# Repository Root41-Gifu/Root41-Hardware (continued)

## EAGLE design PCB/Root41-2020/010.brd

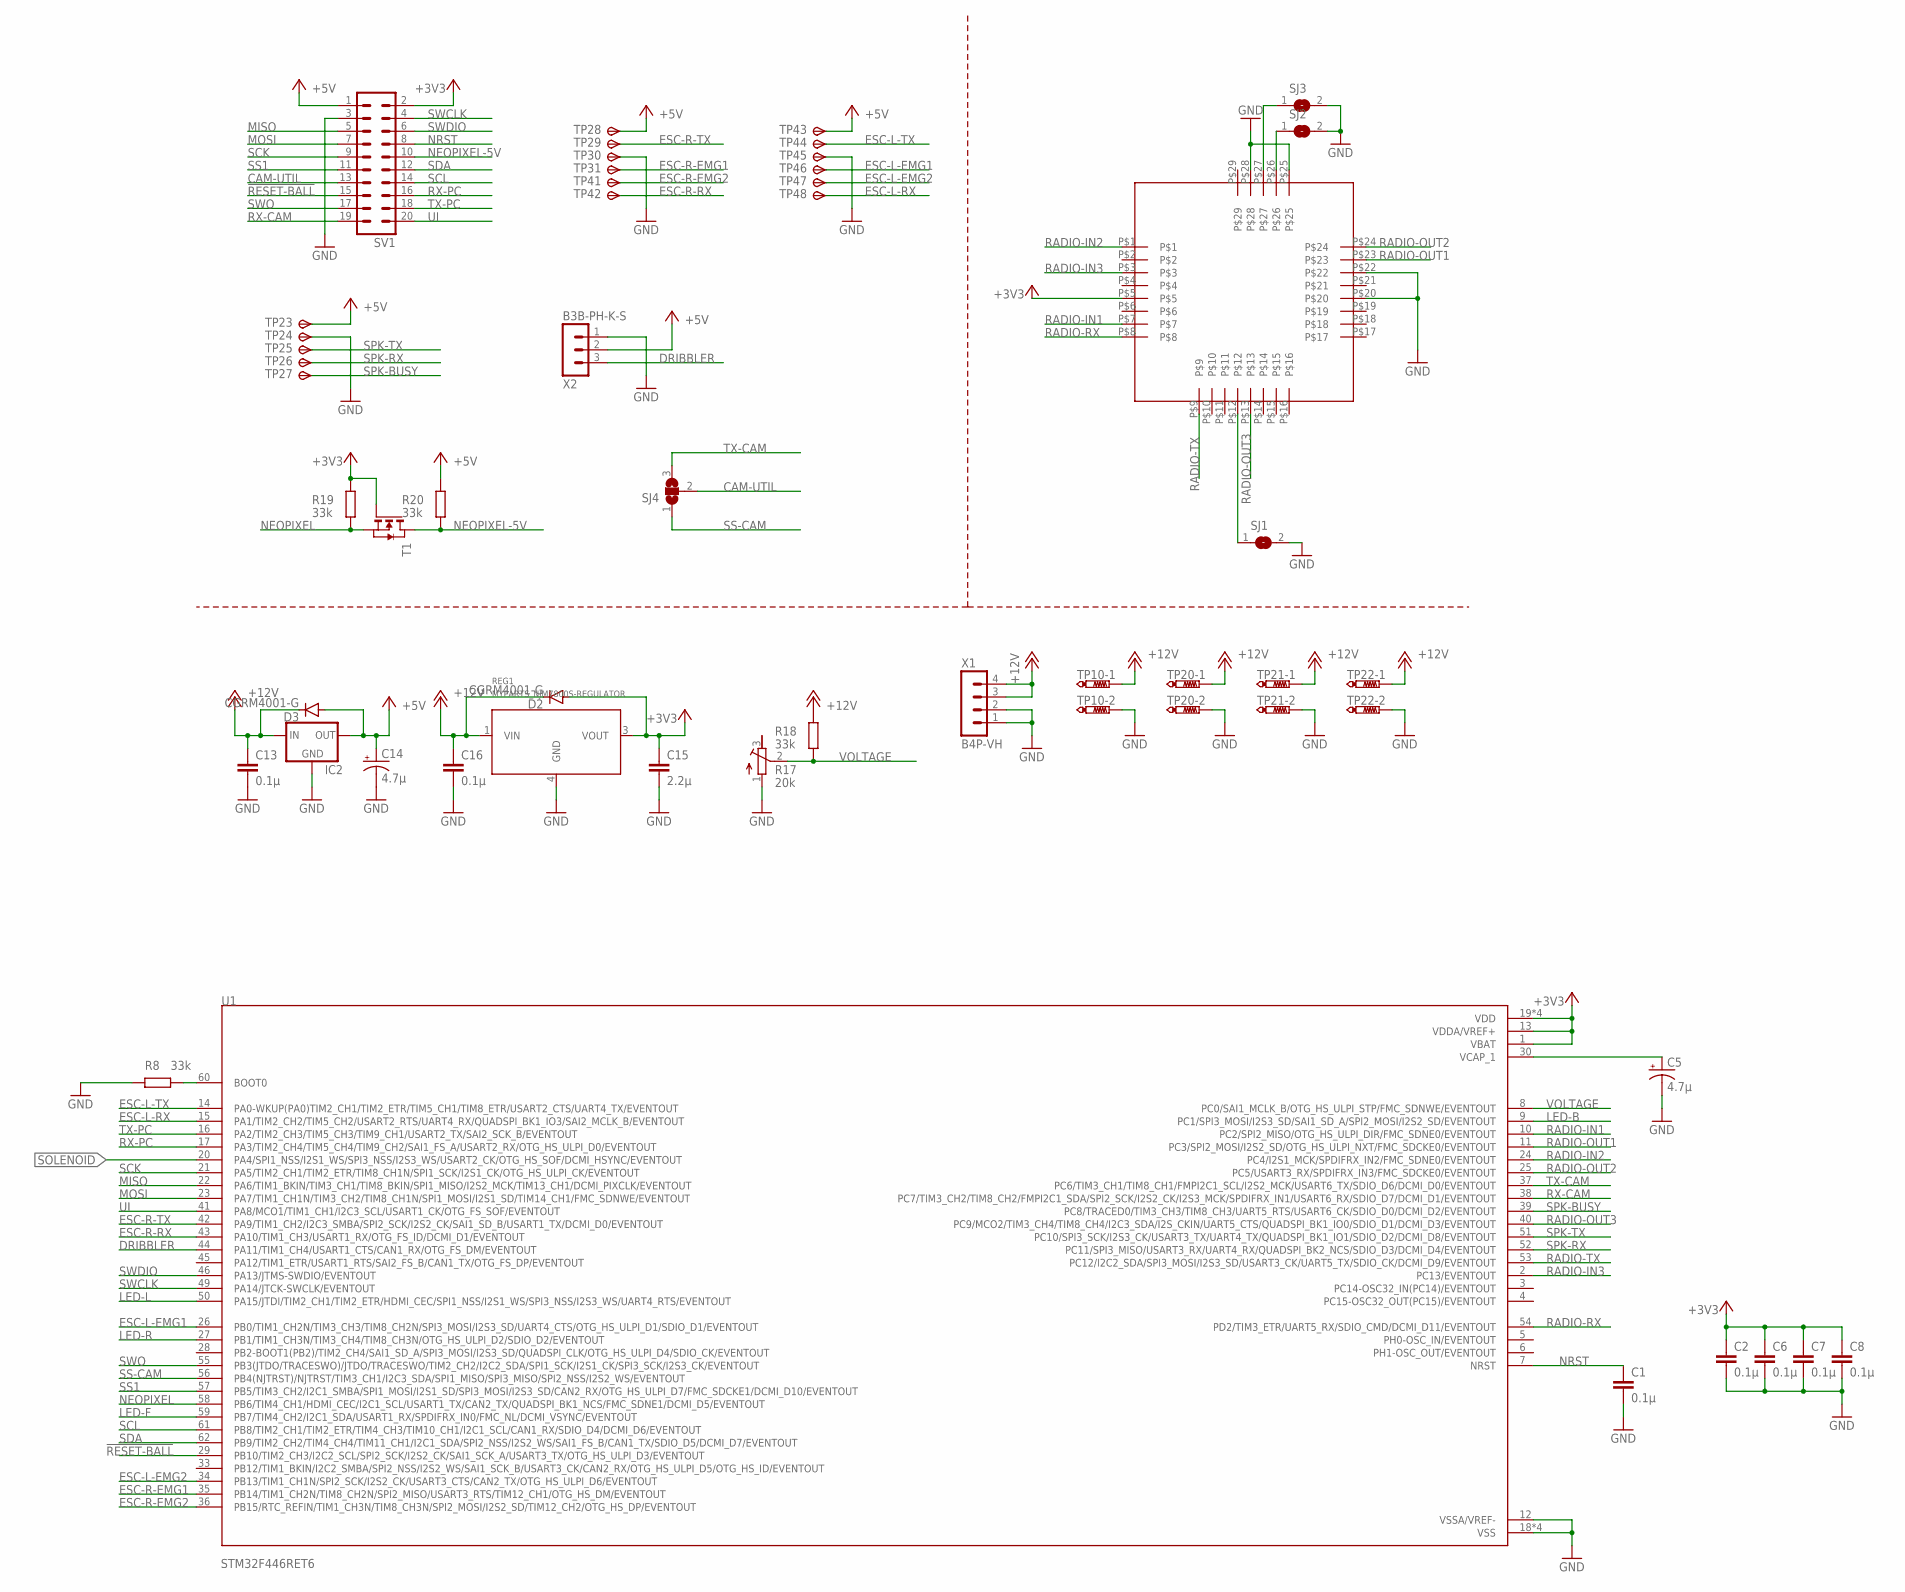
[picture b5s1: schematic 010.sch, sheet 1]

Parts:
C1, C2, C6, C7, C8, C13, C16: 0.1μ; C1608
C5, C14: 4.7μ; SANYO-OSCON_SMD_B6
C15: 2.2μ; C1608
D2, D3: CGRM4001-G; SOD-123_MINI-SMA
IC2: 78XXS
R8, R18, R19, R20: 33k; R0603
R17: 20k; RTRIM3296W
REG1: MYPARTS_NJM7800S-REGULATOR; MYPARTS_D-PAK_TO252AA
SJ1, SJ2, SJ3: SJ
SJ4: SJ2W; SJ_2
SV1: ML20
T1: NMOSSOT23; SOT-23
TP10, TP20, TP21, TP22: PTR2; P2-38-17
TP23, TP28, TP43: TPSTP09SQ; TP09SQ
TP24, TP25, TP26, TP27, TP29, TP30, TP31, TP41, TP42, TP44, TP45, TP46, TP47, TP48: TPSTP09R; TP09R
U1: STM32F446RET6; QFP50P1200X1200X160-64N
U$1: LITE
X1: B4P-VH
X2: B3B-PH-K-S

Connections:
!RESET-BALL: SV1.15, U1.29 (PB10/TIM2_CH3/I2C2_SCL/SPI2_SCK/I2S2_CK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)
+3V3: C2.1, C6.1, C7.1, C8.1, C15.1, D2.A, R19.2, REG1.3 (VOUT), SV1.2, T1.3 (G), U1.1 (VBAT), U1.13 (VDDA/VREF+), U1.19 (VDD), U1.32 (VDD), U1.48 (VDD), U1.64 (VDD), U$1.P$5; also elsewhere on the board
+5V: C14.+, D3.A, IC2.OUT, R20.2, SV1.1, TP23.TP, TP28.TP, TP43.TP, X2.2; also elsewhere on the board
+12V: C13.1, C16.1, D2.C, D3.C, IC2.IN, R18.2, REG1.1 (VIN), TP10.TP-1, TP20.TP-1, TP21.TP-1, TP22.TP-1, X1.3, X1.4; also elsewhere on the board
CAM-UTIL: SJ4.2, SV1.13
DRIBBLER: U1.44 (PA11/TIM1_CH4/USART1_CTS/CAN1_RX/OTG_FS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), X2.3
ESC-L-EMG1: TP46.TP, U1.26 (PB0/TIM1_CH2N/TIM3_CH3/TIM8_CH2N/SPI3_M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)
ESC-L-EMG2: TP47.TP, U1.34 (PB13/TIM1_CH1N/SPI2_SCK/I2S2_CK/USART3_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)
ESC-L-RX: TP48.TP, U1.15 (PA1/TIM2_CH2/TIM5_CH2/USART2_RTS/UART4_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)
ESC-L-TX: TP44.TP, U1.14 (PA0-WKUP(PA0)TIM2_CH1/TIM2_ETR/TIM5_CH1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)
ESC-R-EMG1: TP31.TP, U1.35 (PB14/TIM1_CH2N/TIM8_CH2N/SPI2_MISO/USAR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)
ESC-R-EMG2: TP41.TP, U1.36 (PB15/RTC_REFIN/TIM1_CH3N/TIM8_CH3N/SPI2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)
ESC-R-RX: TP42.TP, U1.43 (PA10/TIM1_CH3/USART1_RX/OTG_FS_ID/DCMI_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)
ESC-R-TX: TP29.TP, U1.42 (PA9/TIM1_CH2/I2C3_SMBA/SPI2_SCK/I2S2_CK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)
GND: C1.2, C2.2, C5.-, C6.2, C7.2, C8.2, C13.2, C14.-, C15.2, C16.2, IC2.GND, R8.2, R17.1 (A), REG1.4 (GND), SJ1.2, SJ2.2, SJ3.2, SV1.3, TP10.TP-2, TP20.TP-2, TP21.TP-2, TP22.TP-2, TP24.TP, TP30.TP, TP45.TP, U1.12 (VSSA/VREF-), U1.18 (VSS), U1.31 (VSS), U1.47 (VSS), U1.63 (VSS), U$1.P$20, U$1.P$22, U$1.P$25, U$1.P$28, X1.1, X1.2, X2.1; also elsewhere on the board
LED-B: U1.9 (PC1/SPI3_MOSI/I2S3_SD/SAI1_SD_A/SPI2_MO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); also elsewhere on the board
LED-F: U1.59 (PB7/TIM4_CH2/I2C1_SDA/USART1_RX/SPDIFRX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); also elsewhere on the board
LED-L: U1.50 (PA15/JTDI/TIM2_CH1/TIM2_ETR/HDMI_CEC/SP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); also elsewhere on the board
LED-R: U1.27 (PB1/TIM1_CH3N/TIM3_CH4/TIM8_CH3N/OTG_HS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); also elsewhere on the board
MISO: SV1.5, U1.22 (PA6/TIM1_BKIN/TIM3_CH1/TIM8_BKIN/SPI1_M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)
MOSI: SV1.7, U1.23 (PA7/TIM1_CH1N/TIM3_CH2/TIM8_CH1N/SPI1_M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)
unnamed: R8.1, U1.60 (BOOT0)
unnamed: C5.+, U1.30 (VCAP_1)
unnamed: SJ1.1, U$1.P$12
unnamed: SJ2.1, U$1.P$26
unnamed: SJ3.1, U$1.P$27
NEOPIXEL: R19.1, T1.2 (S), U1.58 (PB6/TIM4_CH1/HDMI_CEC/I2C1_SCL/USART1_T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)
NEOPIXEL-5V: R20.1, SV1.10, T1.1 (D)
NRST: C1.1, SV1.8, U1.7 (NRST)
RADIO-IN1: U1.10 (PC2/SPI2_MISO/OTG_HS_ULPI_DIR/FMC_SDNE0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), U$1.P$7
RADIO-IN2: U1.24 (PC4/I2S1_MCK/SPDIFRX_IN2/FMC_SDNE0/EVEN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), U$1.P$1
RADIO-IN3: U1.2 (PC13/EVENTOUT), U$1.P$3
RADIO-OUT1: U1.11 (PC3/SPI2_MOSI/I2S2_SD/OTG_HS_ULPI_NXT/F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), U$1.P$23
RADIO-OUT2: U1.25 (PC5/USART3_RX/SPDIFRX_IN3/FMC_SDCKE0/EV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), U$1.P$24
RADIO-OUT3: U1.40 (PC9/MCO2/TIM3_CH4/TIM8_CH4/I2C3_SDA/I2S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), U$1.P$13
RADIO-RX: U1.54 (PD2/TIM3_ETR/UART5_RX/SDIO_CMD/DCMI_D11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), U$1.P$8
RADIO-TX: U1.53 (PC12/I2C2_SDA/SPI3_MOSI/I2S3_SD/USART3_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), U$1.P$9
RX-CAM: SV1.19, U1.38 (PC7/TIM3_CH2/TIM8_CH2/FMPI2C1_SDA/SPI2_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)
RX-PC: SV1.16, U1.17 (PA3/TIM2_CH4/TIM5_CH4/TIM9_CH2/SAI1_FS_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)
SCK: SV1.9, U1.21 (PA5/TIM2_CH1/TIM2_ETR/TIM8_CH1N/SPI1_SC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)
SCL: SV1.14, U1.61 (PB8/TIM2_CH1/TIM2_ETR/TIM4_CH3/TIM10_CH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); also elsewhere on the board
SDA: SV1.12, U1.62 (PB9/TIM2_CH2/TIM4_CH4/TIM11_CH1/I2C1_SD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); also elsewhere on the board
SOLENOID: U1.20 (PA4/SPI1_NSS/I2S1_WS/SPI3_NSS/I2S3_WS/U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); also elsewhere on the board
SPK-BUSY: TP27.TP, U1.39 (PC8/TRACED0/TIM3_CH3/TIM8_CH3/UART5_RTS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)
SPK-RX: TP26.TP, U1.52 (PC11/SPI3_MISO/USART3_RX/UART4_RX/QUADS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)
SPK-TX: TP25.TP, U1.51 (PC10/SPI3_SCK/I2S3_CK/USART3_TX/UART4_T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)
SS1: SV1.11, U1.57 (PB5/TIM3_CH2/I2C1_SMBA/SPI1_MOSI/I2S1_S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)
SS-CAM: SJ4.1, U1.56 (PB4(NJTRST)/NJTRST/TIM3_CH1/I2C3_SDA/SP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)
SWCLK: SV1.4, U1.49 (PA14/JTCK-SWCLK/EVENTOUT)
SWDIO: SV1.6, U1.46 (PA13/JTMS-SWDIO/EVENTOUT)
SWO: SV1.17, U1.55 (PB3(JTDO/TRACESWO)/JTDO/TRACESWO/TIM2_C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)
TX-CAM: SJ4.3, U1.37 (PC6/TIM3_CH1/TIM8_CH1/FMPI2C1_SCL/I2S2_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)
TX-PC: SV1.18, U1.16 (PA2/TIM2_CH3/TIM5_CH3/TIM9_CH1/USART2_T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)
UI: SV1.20, U1.41 (PA8/MCO1/TIM1_CH1/I2C3_SCL/USART1_CK/OT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)
VOLTAGE: R17.2 (S), R18.1, U1.8 (PC0/SAI1_MCLK_B/OTG_HS_ULPI_STP/FMC_SDN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)

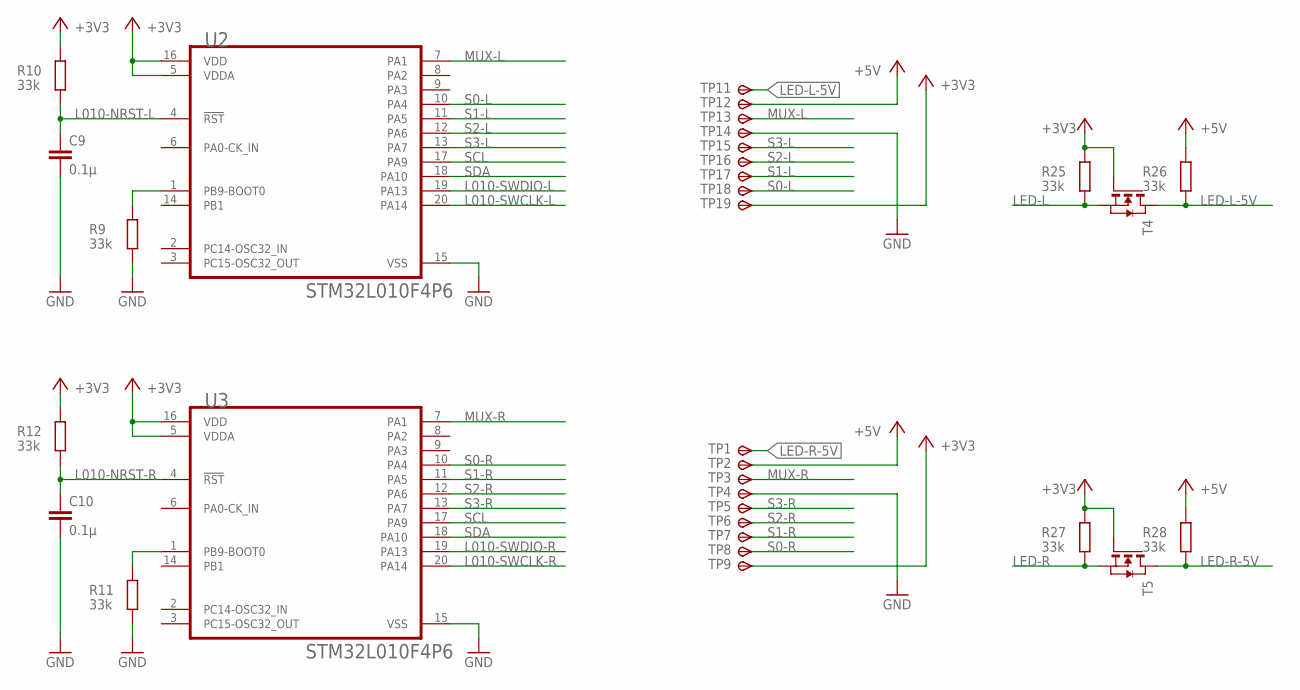
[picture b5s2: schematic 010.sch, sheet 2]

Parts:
C9, C10: 0.1μ; C1608
R9, R10, R11, R12, R25, R26, R27, R28: 33k; R0603
T4, T5: NMOSSOT23; SOT-23
TP1, TP11: TPSTP09SQ; TP09SQ
TP2, TP3, TP4, TP5, TP6, TP7, TP8, TP9, TP12, TP13, TP14, TP15, TP16, TP17, TP18, TP19: TPSTP09R; TP09R
U2, U3: STMICROELECTRONICS_STM32L010F4P6STMICROELECTRONIC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; STMICROELECTRONICS_STM32L010F4P6_2

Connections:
+3V3: R10.2, R12.2, R25.2, R27.2, T4.3 (G), T5.3 (G), TP9.TP, TP19.TP, U2.5 (VDDA), U2.16 (VDD), U3.5 (VDDA), U3.16 (VDD); also elsewhere on the board
+5V: R26.2, R28.2, TP2.TP, TP12.TP; also elsewhere on the board
GND: C9.2, C10.2, R9.1, R11.1, TP4.TP, TP14.TP, U2.15 (VSS), U3.15 (VSS); also elsewhere on the board
L010-NRST-L: C9.1, R10.1, U2.4 (!RST!)
L010-NRST-R: C10.1, R12.1, U3.4 (!RST!)
L010-SWCLK-L: U2.20 (PA14)
L010-SWCLK-R: U3.20 (PA14)
L010-SWDIO-L: U2.19 (PA13)
L010-SWDIO-R: U3.19 (PA13)
LED-L: R25.1, T4.2 (S); also elsewhere on the board
LED-L-5V: R26.1, T4.1 (D), TP11.TP
LED-R: R27.1, T5.2 (S); also elsewhere on the board
LED-R-5V: R28.1, T5.1 (D), TP1.TP
MUX-L: TP13.TP, U2.7 (PA1)
MUX-R: TP3.TP, U3.7 (PA1)
unnamed: R11.2, U3.1 (PB9-BOOT0)
unnamed: R9.2, U2.1 (PB9-BOOT0)
S0-L: TP18.TP, U2.10 (PA4)
S0-R: TP8.TP, U3.10 (PA4)
S1-L: TP17.TP, U2.11 (PA5)
S1-R: TP7.TP, U3.11 (PA5)
S2-L: TP16.TP, U2.12 (PA6)
S2-R: TP6.TP, U3.12 (PA6)
S3-L: TP15.TP, U2.13 (PA7)
S3-R: TP5.TP, U3.13 (PA7)
SCL: U2.17 (PA9), U3.17 (PA9); also elsewhere on the board
SDA: U2.18 (PA10), U3.18 (PA10); also elsewhere on the board

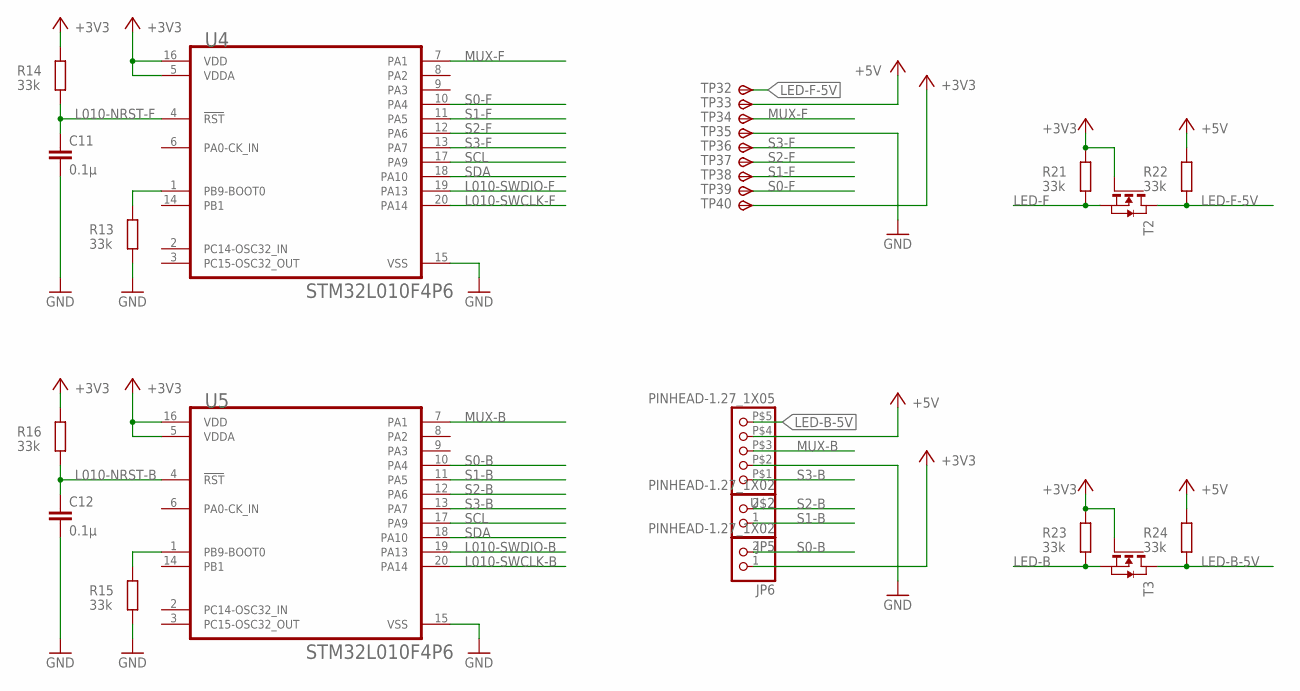
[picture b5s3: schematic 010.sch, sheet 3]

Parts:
C11, C12: 0.1μ; C1608
JP5, JP6: PINHEAD-1.27_1X02
R13, R14, R15, R16, R21, R22, R23, R24: 33k; R0603
T2, T3: NMOSSOT23; SOT-23
TP32: TPSTP09SQ; TP09SQ
TP33, TP34, TP35, TP36, TP37, TP38, TP39, TP40: TPSTP09R; TP09R
U4, U5: STMICROELECTRONICS_STM32L010F4P6STMICROELECTRONIC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; STMICROELECTRONICS_STM32L010F4P6_2
U$2: PINHEAD-1.27_1X05

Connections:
+3V3: JP6.1, R14.2, R16.2, R21.2, R23.2, T2.3 (G), T3.3 (G), TP40.TP, U4.5 (VDDA), U4.16 (VDD), U5.5 (VDDA), U5.16 (VDD); also elsewhere on the board
+5V: R22.2, R24.2, TP33.TP, U$2.P$4 (4); also elsewhere on the board
GND: C11.2, C12.2, R13.1, R15.1, TP35.TP, U4.15 (VSS), U5.15 (VSS), U$2.P$2 (2); also elsewhere on the board
L010-NRST-B: C12.1, R16.1, U5.4 (!RST!)
L010-NRST-F: C11.1, R14.1, U4.4 (!RST!)
L010-SWCLK-B: U5.20 (PA14)
L010-SWCLK-F: U4.20 (PA14)
L010-SWDIO-B: U5.19 (PA13)
L010-SWDIO-F: U4.19 (PA13)
LED-B: R23.1, T3.2 (S); also elsewhere on the board
LED-B-5V: R24.1, T3.1 (D), U$2.P$5 (5)
LED-F: R21.1, T2.2 (S); also elsewhere on the board
LED-F-5V: R22.1, T2.1 (D), TP32.TP
MUX-B: U5.7 (PA1), U$2.P$3 (3)
MUX-F: TP34.TP, U4.7 (PA1)
unnamed: R13.2, U4.1 (PB9-BOOT0)
unnamed: R15.2, U5.1 (PB9-BOOT0)
S0-B: JP6.2, U5.10 (PA4)
S0-F: TP39.TP, U4.10 (PA4)
S1-B: JP5.1, U5.11 (PA5)
S1-F: TP38.TP, U4.11 (PA5)
S2-B: JP5.2, U5.12 (PA6)
S2-F: TP37.TP, U4.12 (PA6)
S3-B: U5.13 (PA7), U$2.P$1 (1)
S3-F: TP36.TP, U4.13 (PA7)
SCL: U4.17 (PA9), U5.17 (PA9); also elsewhere on the board
SDA: U4.18 (PA10), U5.18 (PA10); also elsewhere on the board

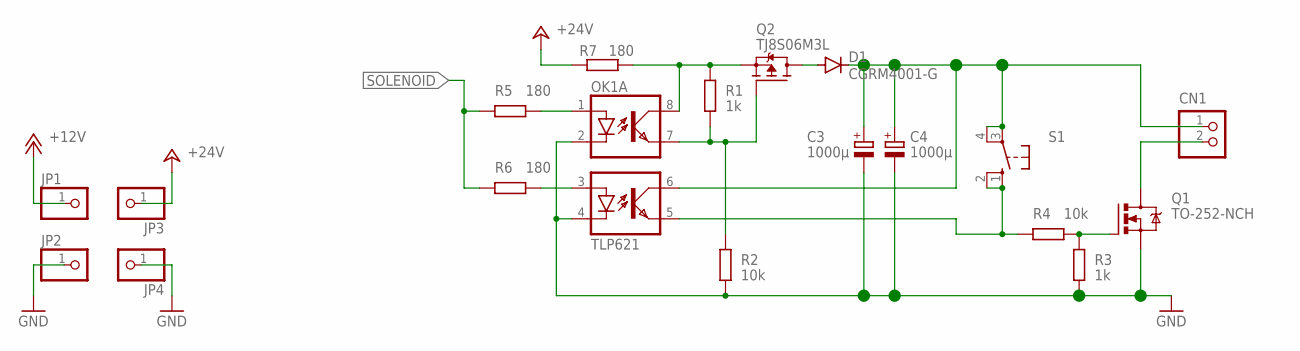
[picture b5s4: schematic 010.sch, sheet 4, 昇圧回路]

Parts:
C3, C4: 1000μ; C12.5
CN1: B2B-PH-K-S
D1: CGRM4001-G; SOD-123_MINI-SMA
JP1, JP2, JP3, JP4: PINHD-1X1; 1X01
OK1: TLP621; DIL08
Q1: TO-252-NCH; D-PAK_TO252AA
Q2: TJ8S06M3L; TO252
R1, R3: 1k; R0603
R2, R4: 10k; R0603
R5, R6: 180; R0603
R7: 180; 0204/7
S1: 10-XX; B3F-10XX

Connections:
+12V: JP1.1; also elsewhere on the board
+24V: JP3.1, R7.1
GND: C3.P$1 (-), C4.P$1 (-), JP2.1, JP4.1, OK1.2 (C), OK1.4 (C), Q1.3 (S), R2.1, R3.1; also elsewhere on the board
unnamed: OK1.3 (A), R6.1
unnamed: OK1.1 (A), R5.1
unnamed: OK1.8 (COL), Q2.2 (S), R1.2, R7.2
unnamed: D1.A, Q2.3 (D)
unnamed: OK1.7 (EMIT), Q2.1 (G), R1.1, R2.2
unnamed: C3.P$2 (+), C4.P$2 (+), CN1.1, D1.C, OK1.6 (COL), S1.3, S1.4 (P1)
unnamed: CN1.2, Q1.4 (D)
unnamed: Q1.1 (G), R3.2, R4.1
unnamed: OK1.5 (EMIT), R4.2, S1.1 (S), S1.2 (S1)
SOLENOID: R5.2, R6.2; also elsewhere on the board

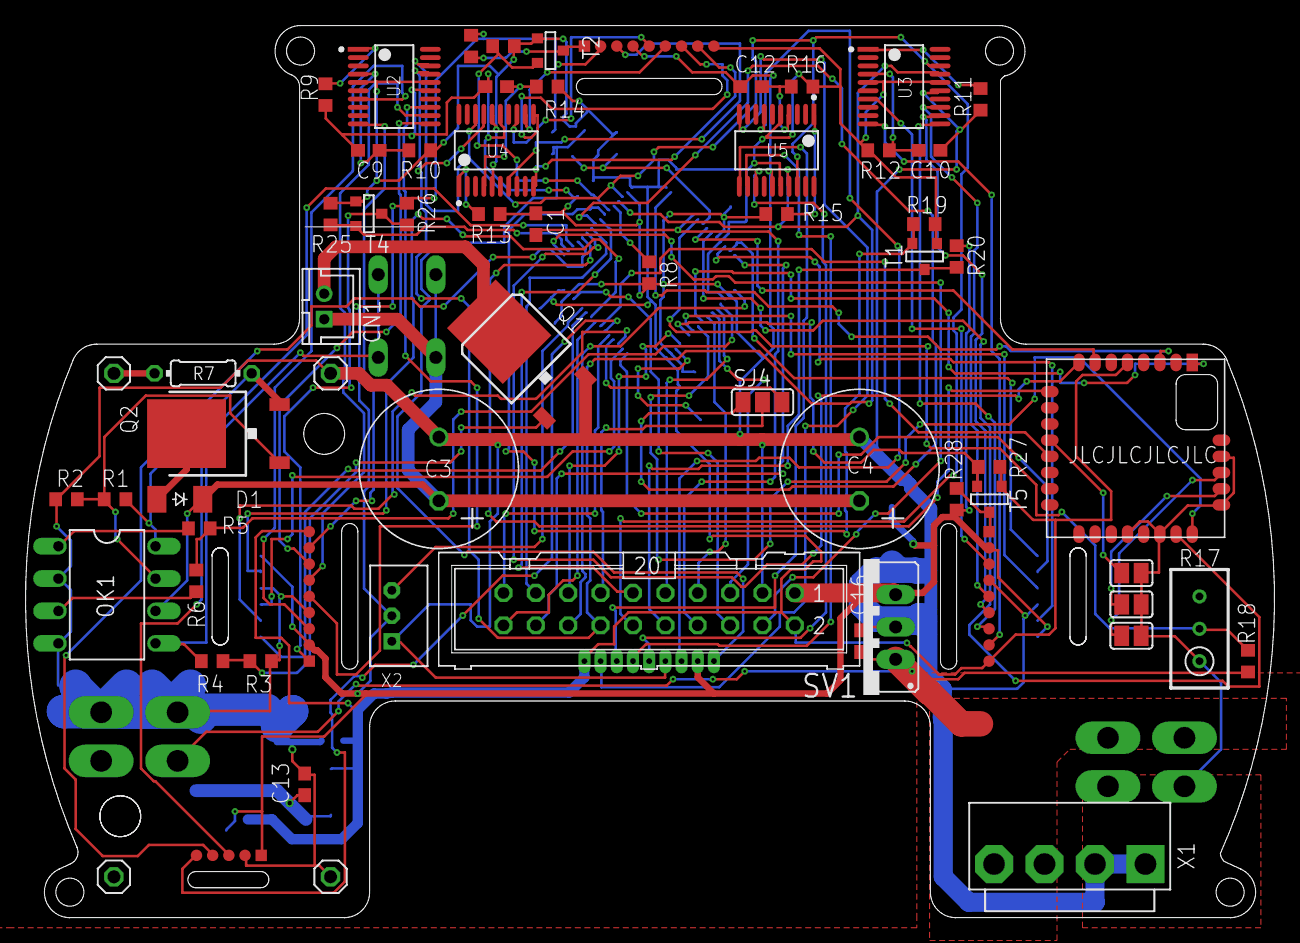
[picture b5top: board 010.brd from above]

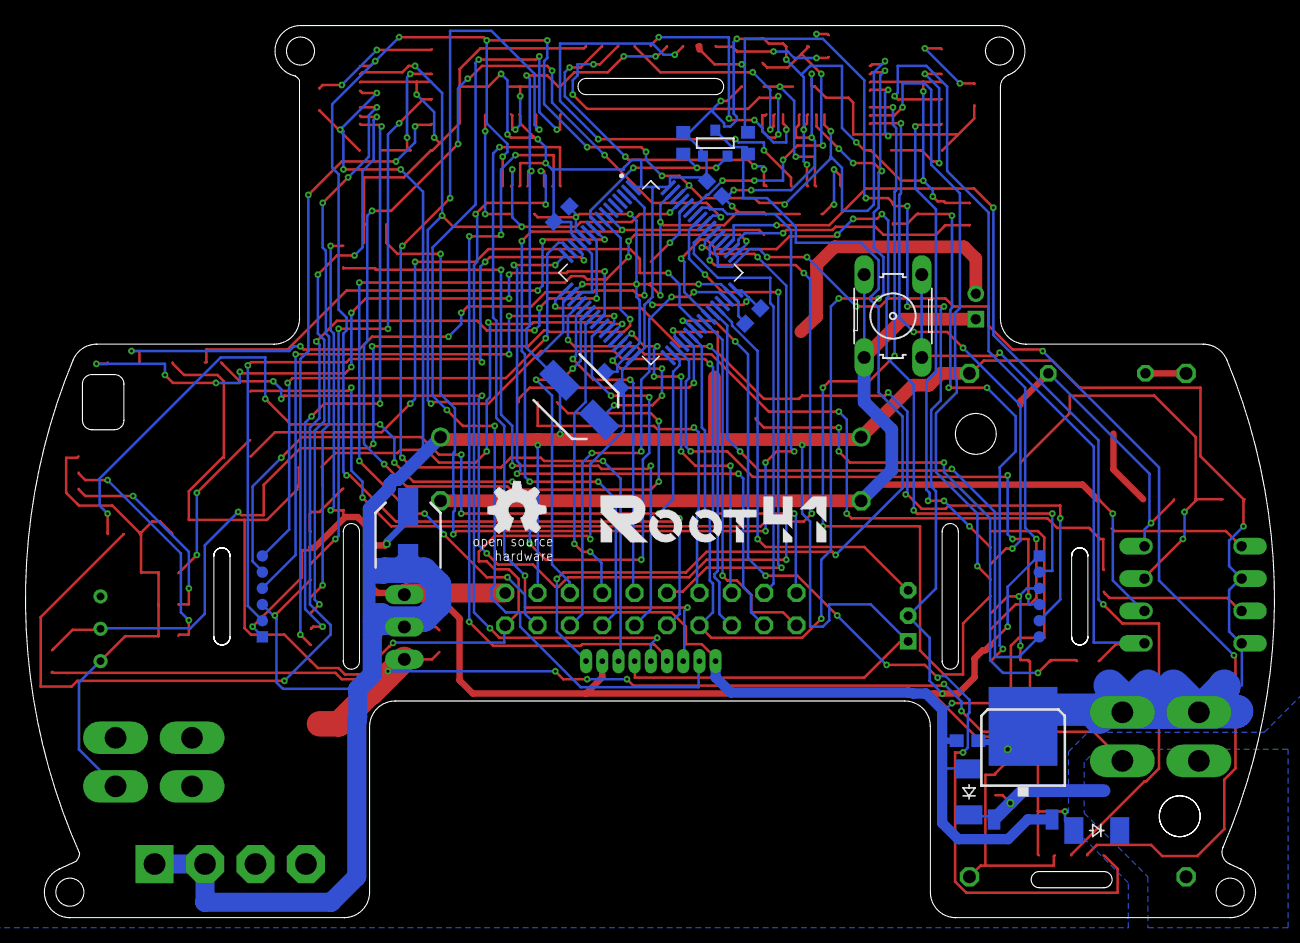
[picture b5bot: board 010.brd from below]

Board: 2 copper layers, 98.0 x 70.0 mm, 128 parts (28 on the bottom side), 97 nets.

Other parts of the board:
U$3: OSHW_5MM

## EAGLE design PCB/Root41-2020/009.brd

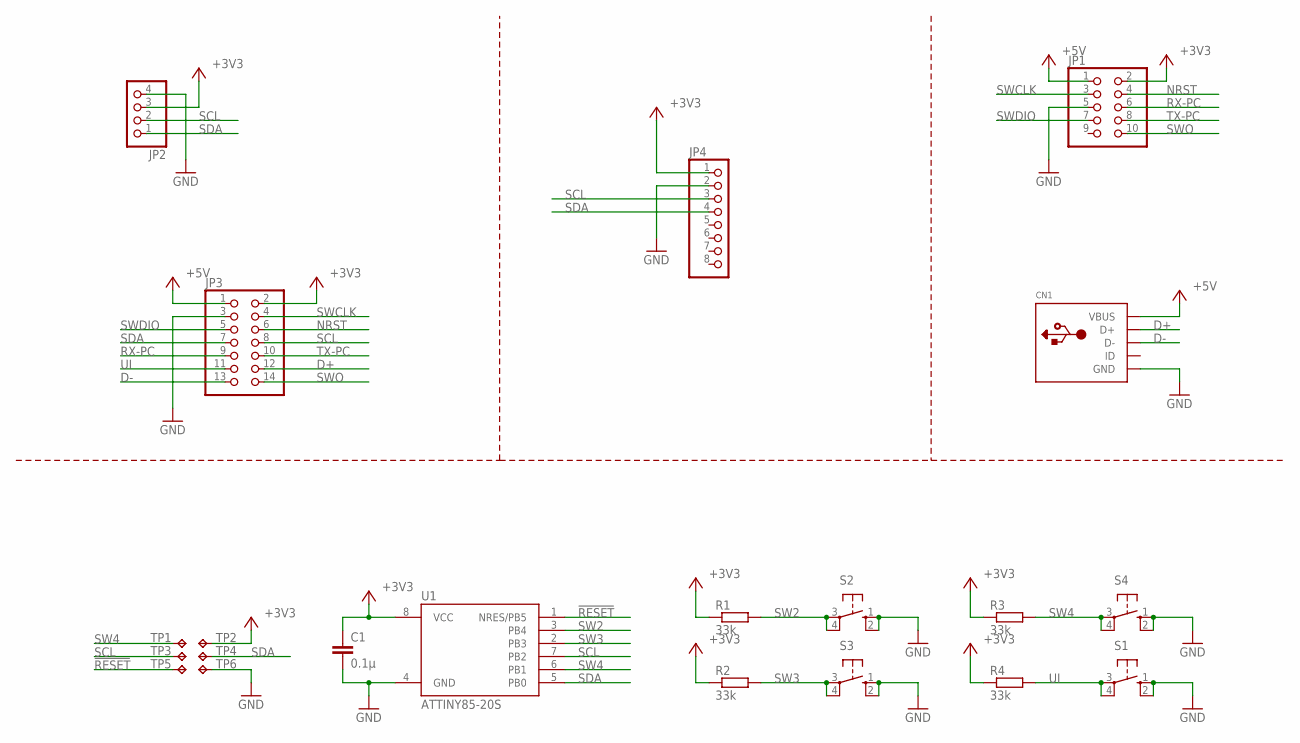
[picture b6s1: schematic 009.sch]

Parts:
C1: 0.1μ; C0603
CN1: USBTHM; USB-MINIB-THM
JP1: PINHD-2X5; 2X05
JP2: PINHD-1X4; 1X04
JP3: PINHD-2X7/90; 2X07/90
JP4: PINHD-1X8; 1X08
R1, R2, R3, R4: 33k; R0603
S1, S2: 40-XX; B3F-40XX
S3, S4: 10-XX; B3F-10XX
TP1: TPTP15SQ; TP15SQ
TP2, TP3, TP4, TP5, TP6: TPTP15R; TP15R
U1: ATTINY85-20S; SOIC8_EIAJ_208MIL

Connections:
!RESET: TP5.TP, U1.1 (NRES/PB5)
+3V3: C1.1, JP1.2, JP2.3, JP3.2, JP4.1, R1.1, R2.1, R3.1, R4.1, TP2.TP, U1.8 (VCC)
+5V: CN1.VBUS, JP1.1, JP3.1
D+: CN1.D+, JP3.12
D-: CN1.D-, JP3.13
GND: C1.2, CN1.GND, JP1.5, JP2.4, JP3.3, JP4.2, S1.1 (S), S1.2 (S1), S2.1 (S), S2.2 (S1), S3.1 (S), S3.2 (S1), S4.1 (S), S4.2 (S1), TP6.TP, U1.4 (GND)
NRST: JP1.4, JP3.6
RX-PC: JP1.6, JP3.9
SCL: JP2.2, JP3.8, JP4.3, TP3.TP, U1.7 (PB2)
SDA: JP2.1, JP3.7, JP4.4, TP4.TP, U1.5 (PB0)
SW2: R1.2, S2.3, S2.4 (P1), U1.3 (PB4)
SW3: R2.2, S3.3, S3.4 (P1), U1.2 (PB3)
SW4: R3.2, S4.3, S4.4 (P1), TP1.TP, U1.6 (PB1)
SWCLK: JP1.3, JP3.4
SWDIO: JP1.7, JP3.5
SWO: JP1.10, JP3.14
TX-PC: JP1.8, JP3.10
UI: JP3.11, R4.2, S1.3, S1.4 (P1)

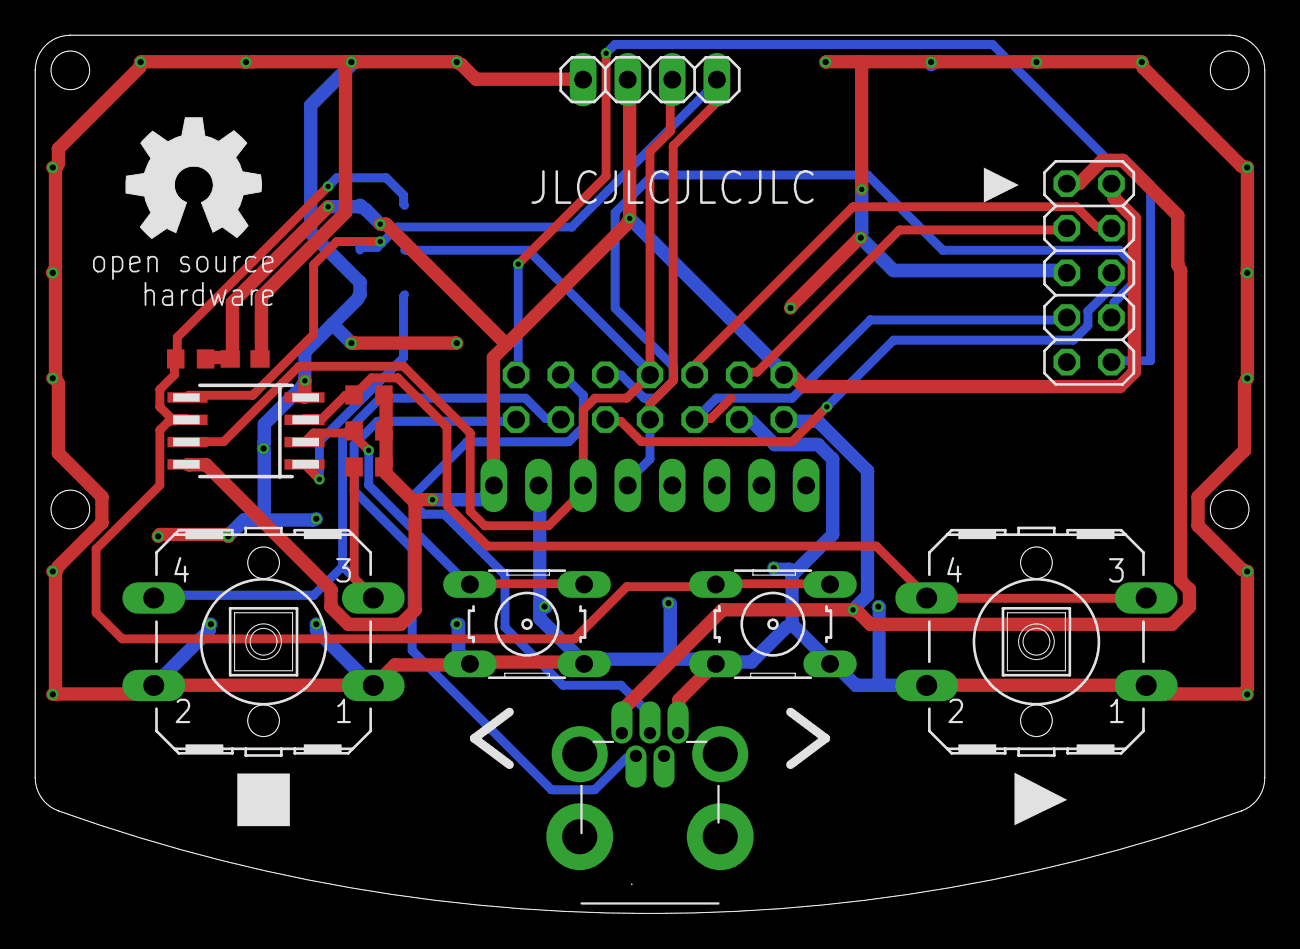
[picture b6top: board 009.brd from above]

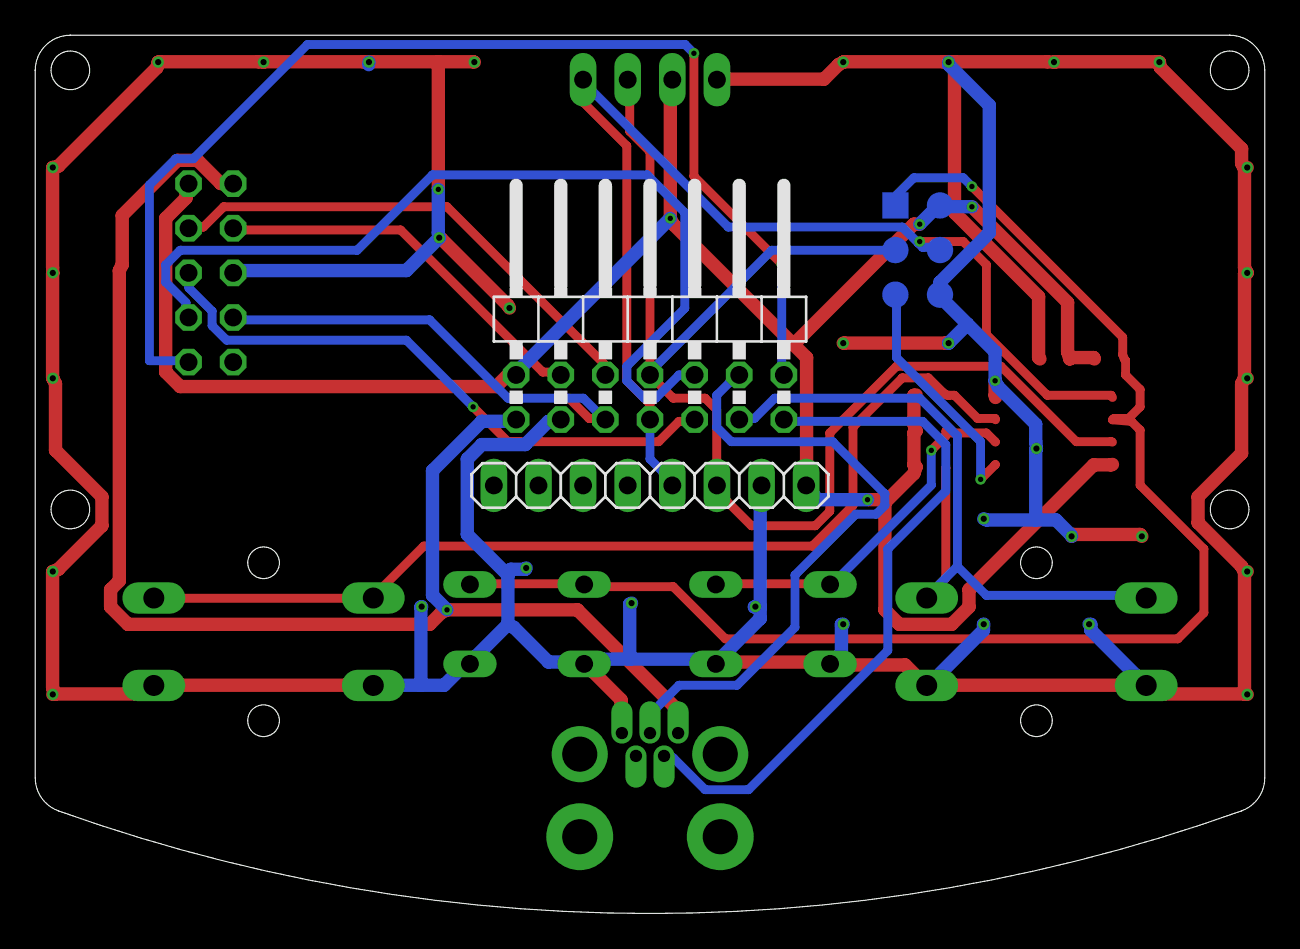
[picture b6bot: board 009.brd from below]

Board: 2 copper layers, 70.0 x 50.0 mm, 22 parts (8 on the bottom side), 18 nets.

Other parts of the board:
U$1: OSHW_8MM

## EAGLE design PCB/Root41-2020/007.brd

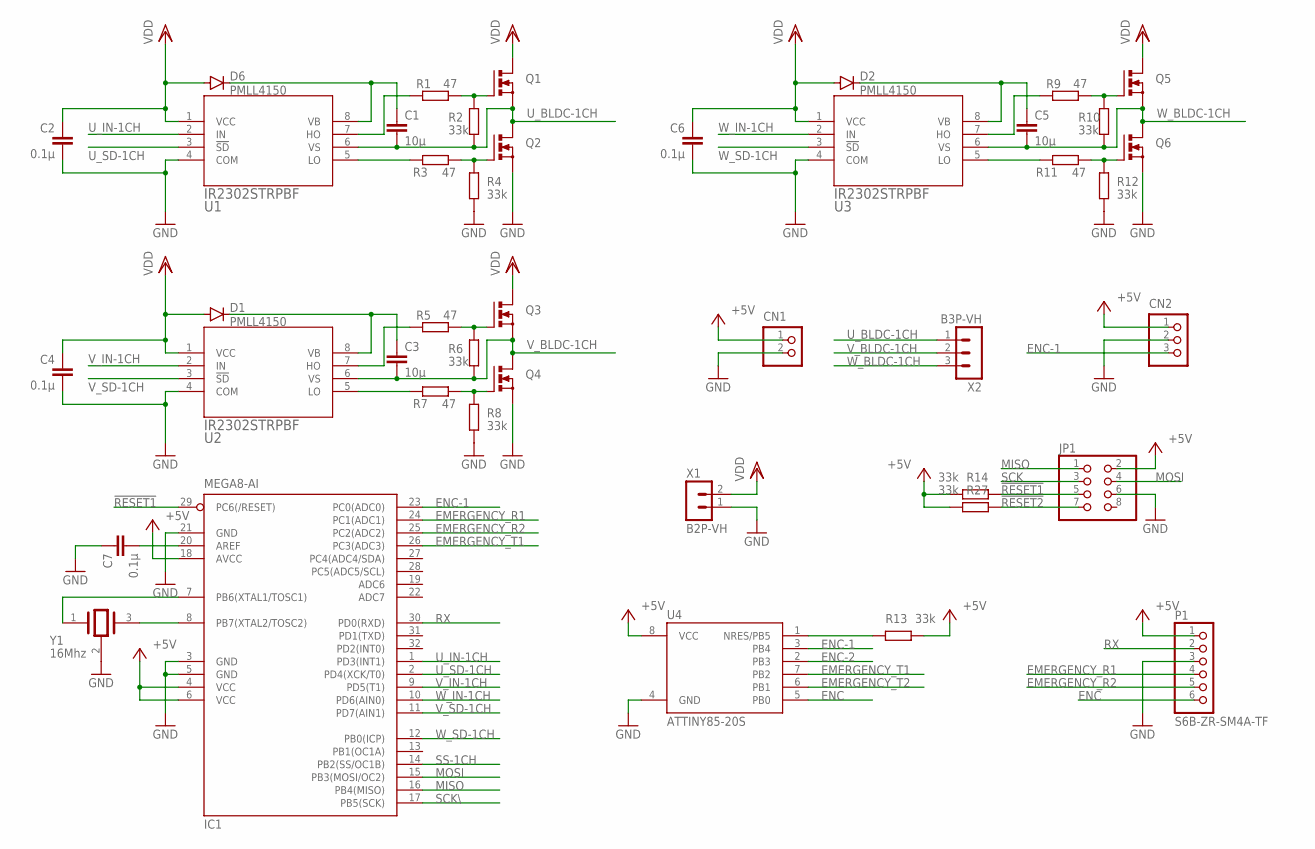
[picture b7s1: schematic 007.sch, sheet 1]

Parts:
C1, C3, C5: 10μ; C1608
C2, C4, C6, C7: 0.1μ; C1608
CN1: B2B-PH-K-S
CN2: B3B-PH-K-S
D1, D2, D6: PMLL4150; SOD80C
IC1: MEGA8-AI; TQFP32-08
JP1: PINHD-2X4; 2X04
P1: S6B-ZR-SM4A-TF; ZH-SM4-SIDE06
Q1, Q2, Q3, Q4, Q5, Q6: N-MOSFET-SO8S; SO-08
R1, R3, R5, R7, R9, R11: 47; R0603
R2, R4, R6, R8, R10, R12, R13, R14, R27: 33k; R0603
U1, U2, U3: IR2302STRPBF; PG-DSO-8-910_INF
U4: ATTINY85-20S; SOIC8_EIAJ_208MIL
X1: B2P-VH
X2: B3P-VH
Y1: 16Mhz; MURATA_CSTNE16M0V53C000R0_0

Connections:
!RESET1: IC1.29 (PC6(/RESET)), JP1.5, R14.2
!RESET2: JP1.7, R27.2; also elsewhere on the board
+5V: CN1.1, CN2.1, IC1.4 (VCC), IC1.6 (VCC), IC1.18 (AVCC), JP1.2, P1.1, R13.1, R14.1, R27.1, U4.8 (VCC); also elsewhere on the board
EMERGENCY_R1: IC1.24 (PC1(ADC1)), P1.4; also elsewhere on the board
EMERGENCY_R2: IC1.25 (PC2(ADC2)), P1.5; also elsewhere on the board
EMERGENCY_T1: IC1.26 (PC3(ADC3)), U4.7 (PB2)
EMERGENCY_T2: U4.6 (PB1); also elsewhere on the board
ENC: P1.6, U4.5 (PB0)
ENC-1: CN2.3, IC1.23 (PC0(ADC0)), U4.3 (PB4)
ENC-2: U4.2 (PB3); also elsewhere on the board
GND: C2.1, C4.1, C6.1, C7.2, CN1.2, CN2.2, IC1.3 (GND), IC1.5 (GND), IC1.21 (GND), JP1.6, P1.3, Q2.1 (S), Q2.2 (S), Q2.3 (S), Q4.1 (S), Q4.2 (S), Q4.3 (S), Q6.1 (S), Q6.2 (S), Q6.3 (S), R4.1, R8.1, R12.1, U1.4 (COM), U2.4 (COM), U3.4 (COM), U4.4 (GND), X1.1, Y1.2 (GND); also elsewhere on the board
MISO: IC1.16 (PB4(MISO)), JP1.1; also elsewhere on the board
MOSI: IC1.15 (PB3(MOSI/OC2)), JP1.4; also elsewhere on the board
unnamed: C3.1, D1.C, U2.8 (VB)
unnamed: C1.1, D6.C, U1.8 (VB)
unnamed: R1.1, U1.7 (HO)
unnamed: R5.1, U2.7 (HO)
unnamed: Q1.4 (G), R1.2, R2.2
unnamed: Q2.4 (G), R3.1, R4.2
unnamed: R3.2, U1.5 (LO)
unnamed: Q3.4 (G), R5.2, R6.2
unnamed: Q4.4 (G), R7.1, R8.2
unnamed: R7.2, U2.5 (LO)
unnamed: C5.1, D2.C, U3.8 (VB)
unnamed: R9.1, U3.7 (HO)
unnamed: Q5.4 (G), R9.2, R10.2
unnamed: Q6.4 (G), R11.1, R12.2
unnamed: R11.2, U3.5 (LO)
unnamed: R13.2, U4.1 (NRES/PB5)
unnamed: IC1.8 (PB7(XTAL2/TOSC2)), Y1.3 (OUTPUT)
unnamed: IC1.7 (PB6(XTAL1/TOSC1)), Y1.1 (INPUT)
unnamed: C7.1, IC1.20 (AREF)
RX: IC1.30 (PD0(RXD)), P1.2; also elsewhere on the board
SS-1CH: IC1.14 (PB2(SS/OC1B))
U_BLDC-1CH: C1.2, Q1.1 (S), Q1.2 (S), Q1.3 (S), Q2.5 (D), Q2.6 (D), Q2.7 (D), Q2.8 (D), R2.1, U1.6 (VS), X2.1
U_IN-1CH: IC1.1 (PD3(INT1)), U1.2 (IN)
U_SD-1CH: IC1.2 (PD4(XCK/T0)), U1.3 (!SD)
VDD: C2.2, C4.2, C6.2, D1.A, D2.A, D6.A, Q1.5 (D), Q1.6 (D), Q1.7 (D), Q1.8 (D), Q3.5 (D), Q3.6 (D), Q3.7 (D), Q3.8 (D), Q5.5 (D), Q5.6 (D), Q5.7 (D), Q5.8 (D), U1.1 (VCC), U2.1 (VCC), U3.1 (VCC), X1.2; also elsewhere on the board
V_BLDC-1CH: C3.2, Q3.1 (S), Q3.2 (S), Q3.3 (S), Q4.5 (D), Q4.6 (D), Q4.7 (D), Q4.8 (D), R6.1, U2.6 (VS), X2.2
V_IN-1CH: IC1.9 (PD5(T1)), U2.2 (IN)
V_SD-1CH: IC1.11 (PD7(AIN1)), U2.3 (!SD)
W_BLDC-1CH: C5.2, Q5.1 (S), Q5.2 (S), Q5.3 (S), Q6.5 (D), Q6.6 (D), Q6.7 (D), Q6.8 (D), R10.1, U3.6 (VS), X2.3
W_IN-1CH: IC1.10 (PD6(AIN0)), U3.2 (IN)
W_SD-1CH: IC1.12 (PB0(ICP)), U3.3 (!SD)

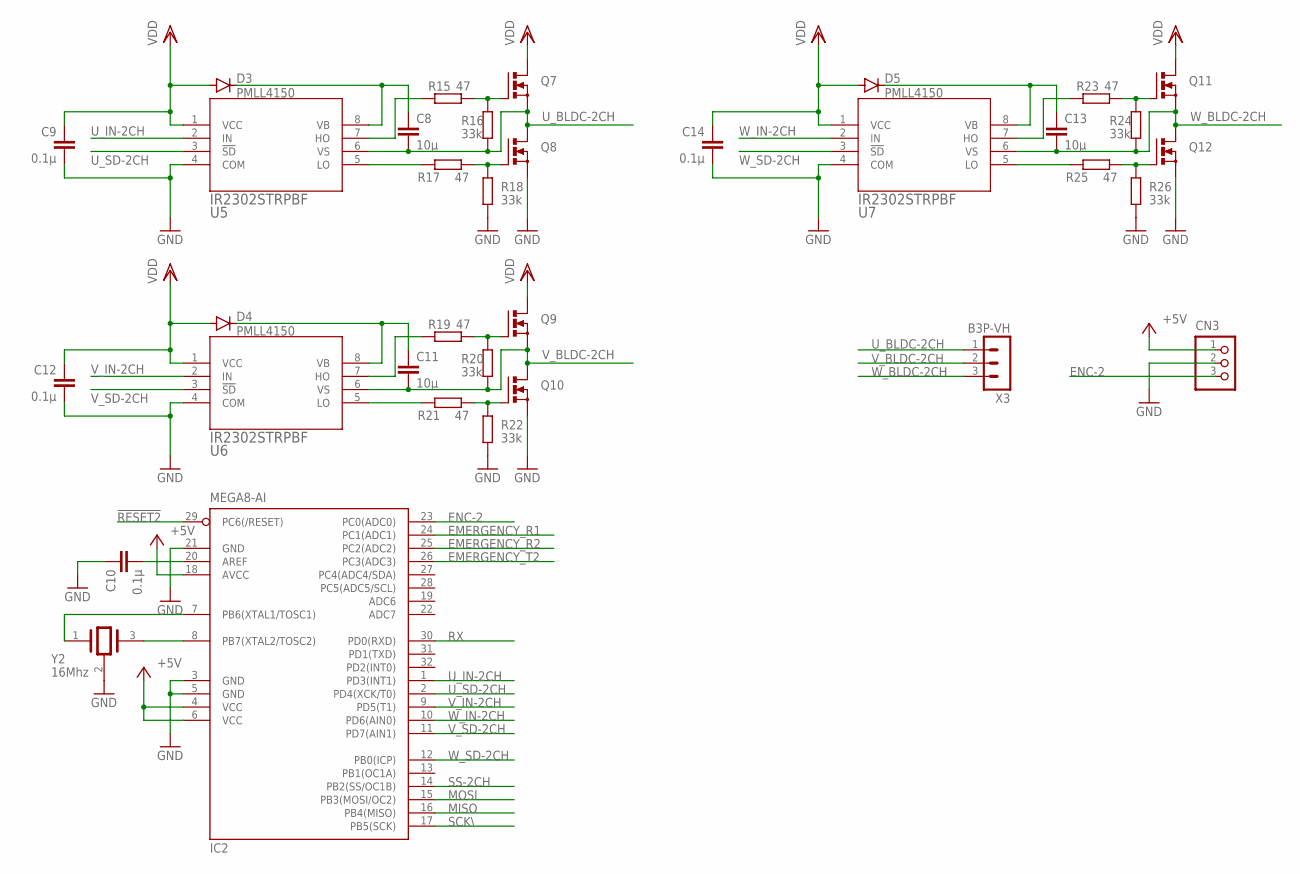
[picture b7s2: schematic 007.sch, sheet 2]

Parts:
C8, C11, C13: 10μ; C1608
C9, C10, C12, C14: 0.1μ; C1608
CN3: B3B-PH-K-S
D3, D4, D5: PMLL4150; SOD80C
IC2: MEGA8-AI; TQFP32-08
Q7, Q8, Q9, Q10, Q11, Q12: N-MOSFET-SO8S; SO-08
R15, R17, R19, R21, R23, R25: 47; R0603
R16, R18, R20, R22, R24, R26: 33k; R0603
U5, U6, U7: IR2302STRPBF; PG-DSO-8-910_INF
X3: B3P-VH
Y2: 16Mhz; MURATA_CSTNE16M0V53C000R0_0

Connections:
!RESET2: IC2.29 (PC6(/RESET)); also elsewhere on the board
+5V: CN3.1, IC2.4 (VCC), IC2.6 (VCC), IC2.18 (AVCC); also elsewhere on the board
EMERGENCY_R1: IC2.24 (PC1(ADC1)); also elsewhere on the board
EMERGENCY_R2: IC2.25 (PC2(ADC2)); also elsewhere on the board
EMERGENCY_T2: IC2.26 (PC3(ADC3)); also elsewhere on the board
ENC-2: CN3.3, IC2.23 (PC0(ADC0)); also elsewhere on the board
GND: C9.1, C10.2, C12.1, C14.1, CN3.2, IC2.3 (GND), IC2.5 (GND), IC2.21 (GND), Q8.1 (S), Q8.2 (S), Q8.3 (S), Q10.1 (S), Q10.2 (S), Q10.3 (S), Q12.1 (S), Q12.2 (S), Q12.3 (S), R18.1, R22.1, R26.1, U5.4 (COM), U6.4 (COM), U7.4 (COM), Y2.2 (GND); also elsewhere on the board
MISO: IC2.16 (PB4(MISO)); also elsewhere on the board
MOSI: IC2.15 (PB3(MOSI/OC2)); also elsewhere on the board
unnamed: C8.1, D3.C, U5.8 (VB)
unnamed: R15.1, U5.7 (HO)
unnamed: Q7.4 (G), R15.2, R16.2
unnamed: Q8.4 (G), R17.1, R18.2
unnamed: R17.2, U5.5 (LO)
unnamed: IC2.8 (PB7(XTAL2/TOSC2)), Y2.3 (OUTPUT)
unnamed: IC2.7 (PB6(XTAL1/TOSC1)), Y2.1 (INPUT)
unnamed: C10.1, IC2.20 (AREF)
unnamed: C11.1, D4.C, U6.8 (VB)
unnamed: R19.1, U6.7 (HO)
unnamed: Q9.4 (G), R19.2, R20.2
unnamed: Q10.4 (G), R21.1, R22.2
unnamed: R21.2, U6.5 (LO)
unnamed: C13.1, D5.C, U7.8 (VB)
unnamed: R23.1, U7.7 (HO)
unnamed: Q11.4 (G), R23.2, R24.2
unnamed: Q12.4 (G), R25.1, R26.2
unnamed: R25.2, U7.5 (LO)
RX: IC2.30 (PD0(RXD)); also elsewhere on the board
SS-2CH: IC2.14 (PB2(SS/OC1B))
U_BLDC-2CH: C8.2, Q7.1 (S), Q7.2 (S), Q7.3 (S), Q8.5 (D), Q8.6 (D), Q8.7 (D), Q8.8 (D), R16.1, U5.6 (VS), X3.1
U_IN-2CH: IC2.1 (PD3(INT1)), U5.2 (IN)
U_SD-2CH: IC2.2 (PD4(XCK/T0)), U5.3 (!SD)
VDD: C9.2, C12.2, C14.2, D3.A, D4.A, D5.A, Q7.5 (D), Q7.6 (D), Q7.7 (D), Q7.8 (D), Q9.5 (D), Q9.6 (D), Q9.7 (D), Q9.8 (D), Q11.5 (D), Q11.6 (D), Q11.7 (D), Q11.8 (D), U5.1 (VCC), U6.1 (VCC), U7.1 (VCC); also elsewhere on the board
V_BLDC-2CH: C11.2, Q9.1 (S), Q9.2 (S), Q9.3 (S), Q10.5 (D), Q10.6 (D), Q10.7 (D), Q10.8 (D), R20.1, U6.6 (VS), X3.2
V_IN-2CH: IC2.9 (PD5(T1)), U6.2 (IN)
V_SD-2CH: IC2.11 (PD7(AIN1)), U6.3 (!SD)
W_BLDC-2CH: C13.2, Q11.1 (S), Q11.2 (S), Q11.3 (S), Q12.5 (D), Q12.6 (D), Q12.7 (D), Q12.8 (D), R24.1, U7.6 (VS), X3.3
W_IN-2CH: IC2.10 (PD6(AIN0)), U7.2 (IN)
W_SD-2CH: IC2.12 (PB0(ICP)), U7.3 (!SD)

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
